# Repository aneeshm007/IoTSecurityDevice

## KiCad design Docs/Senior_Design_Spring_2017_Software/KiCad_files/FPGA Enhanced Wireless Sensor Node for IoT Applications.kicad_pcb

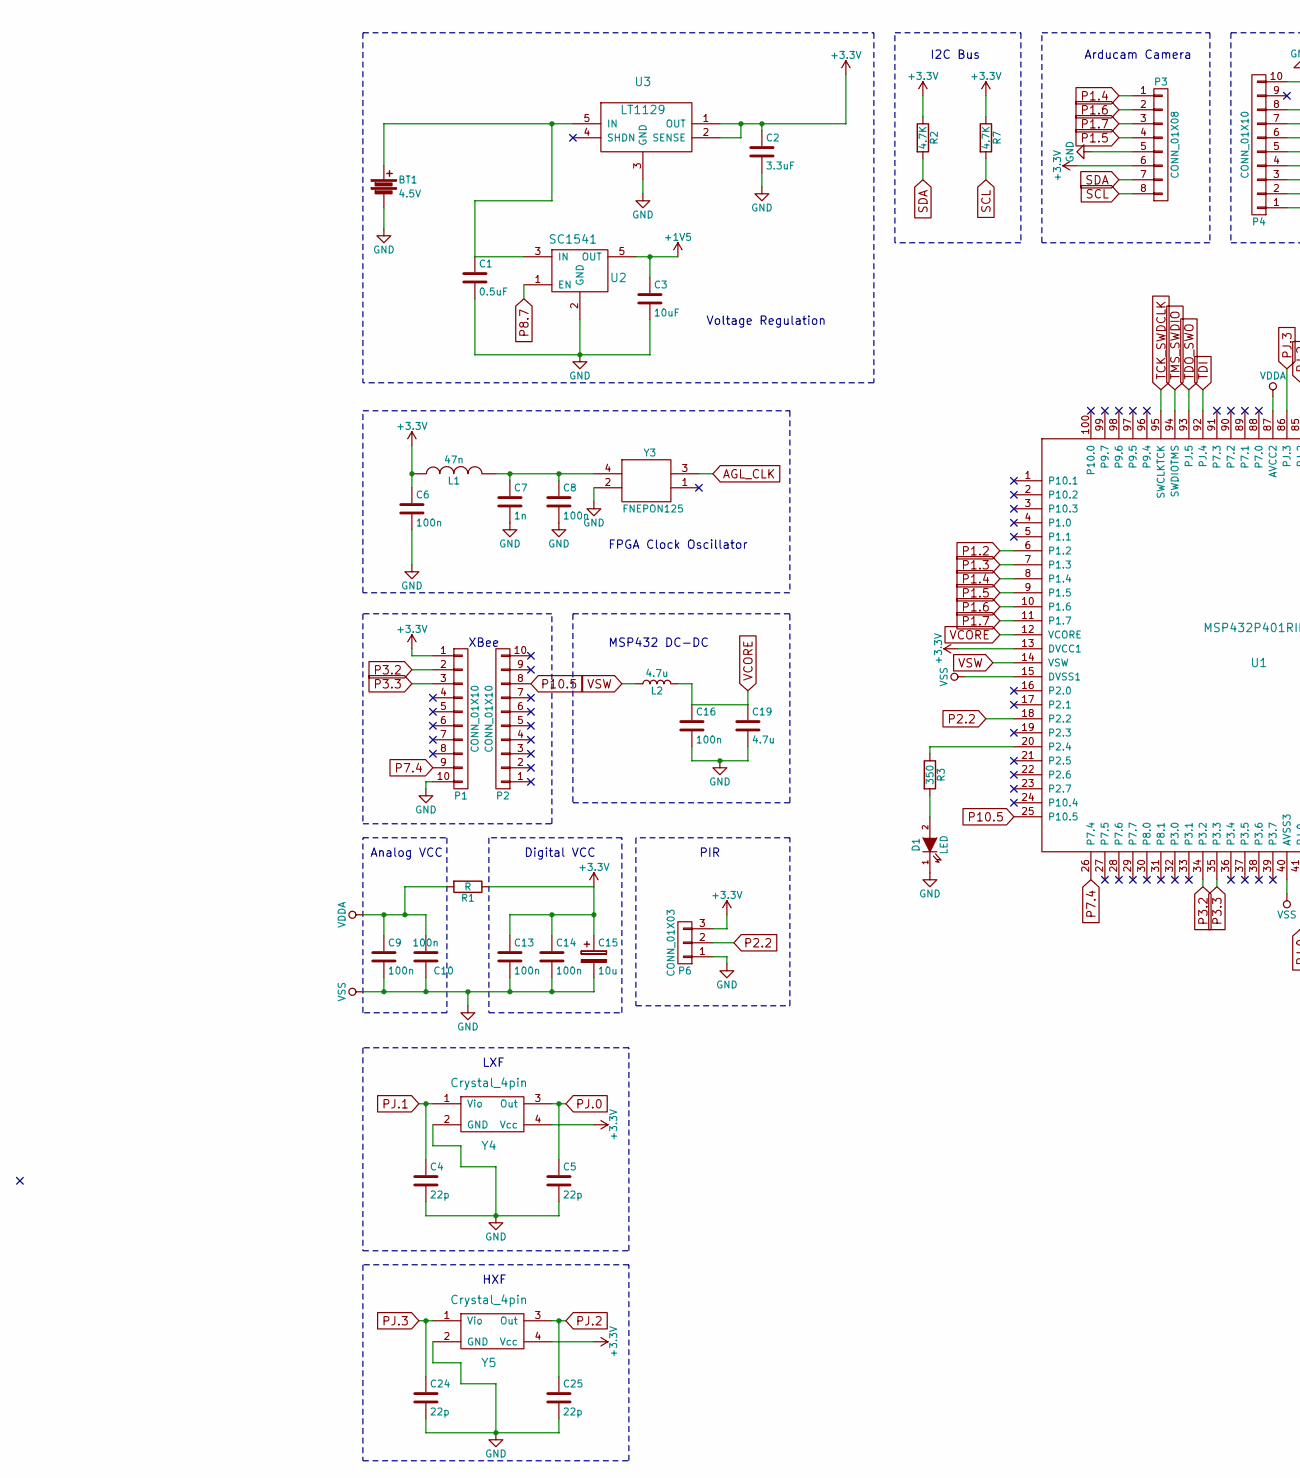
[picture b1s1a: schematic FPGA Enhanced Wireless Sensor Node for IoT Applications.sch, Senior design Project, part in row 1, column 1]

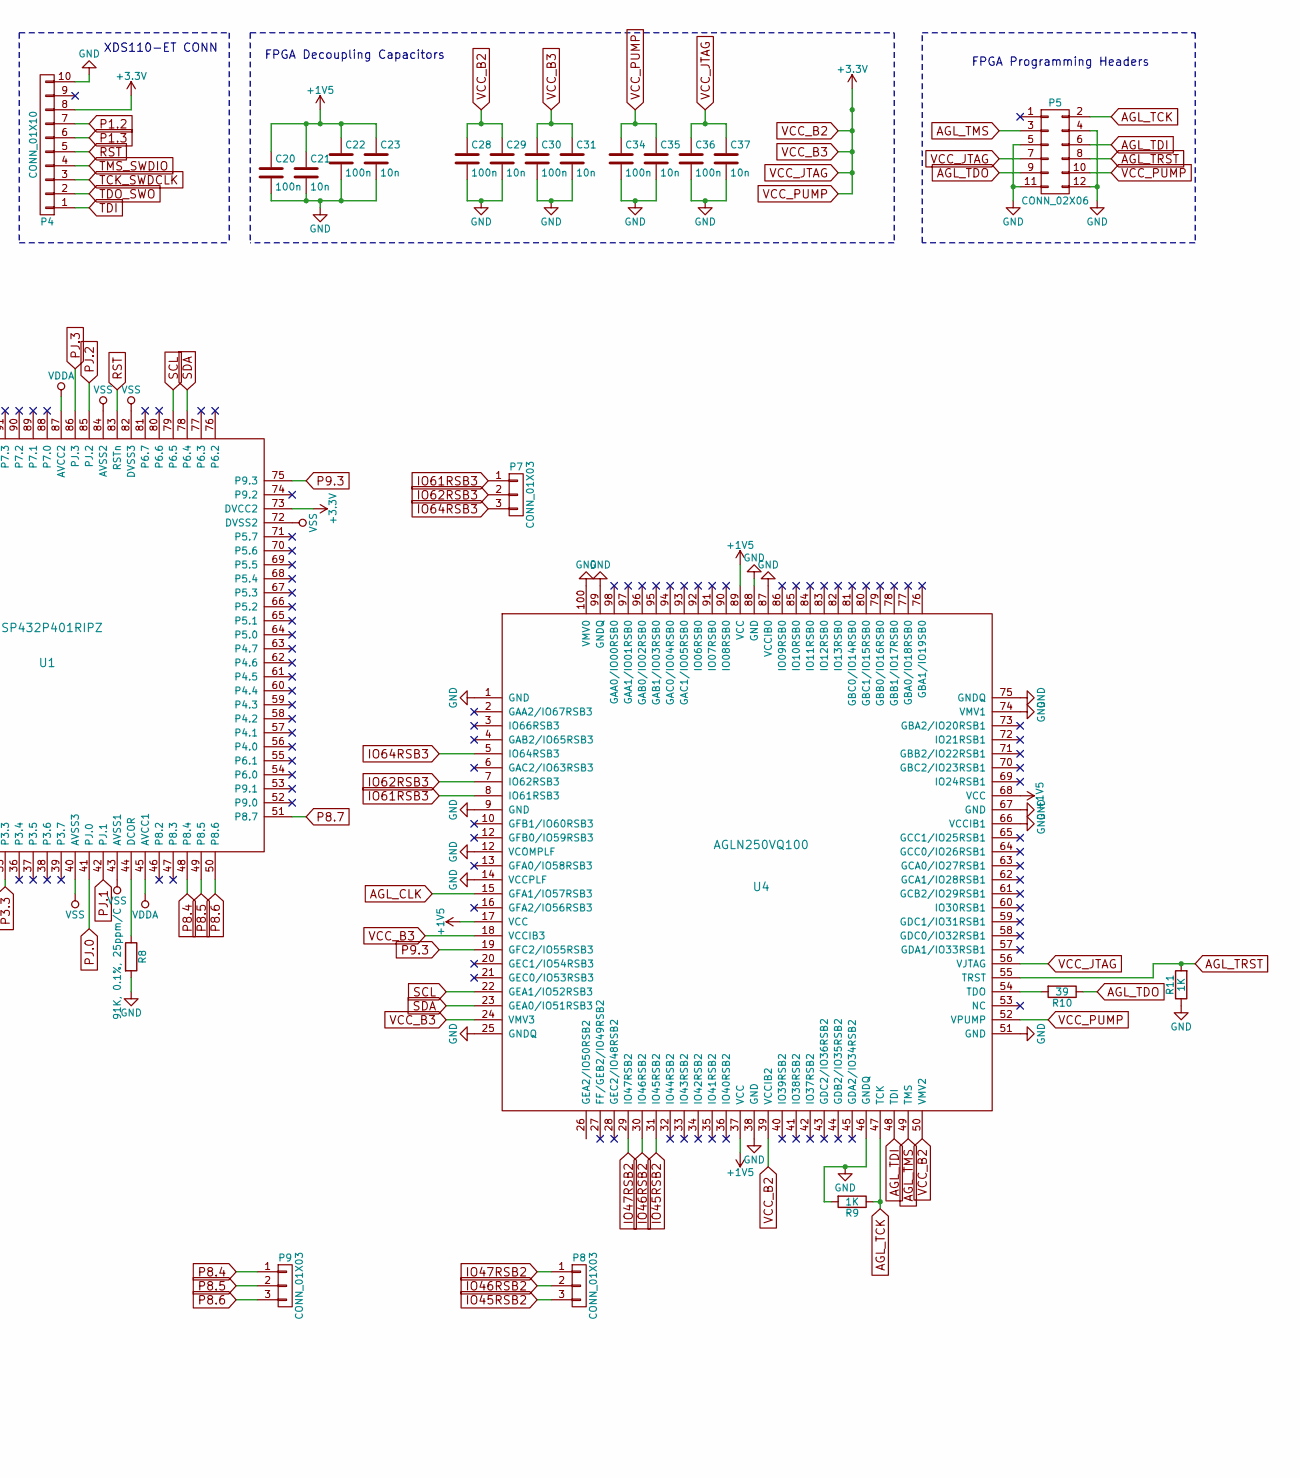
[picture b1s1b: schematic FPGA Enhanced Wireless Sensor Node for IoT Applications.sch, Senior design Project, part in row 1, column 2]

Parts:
BT1: 4.5V; Pin_Header_Straight_1x02_Pitch2.54mm
C1: 0.5uF; C_0603_HandSoldering
C2: 3.3uF; C_0805_HandSoldering
C3: 10uF; C_0805_HandSoldering
C4, C5, C24, C25: 22p; C_0603_HandSoldering
C6, C8, C9, C10, C13, C14, C16, C20, C22, C28, C30, C34, C36: 100n; C_0603_HandSoldering
C7: 1n; C_0603_HandSoldering
C15: 10u; C_0805_HandSoldering
C19: 4.7u; C_0603_HandSoldering
C21, C23, C29, C31, C35, C37: 10n; C_0603_HandSoldering
D1: LED; LED_0805
L1: 47n; C_0603_HandSoldering
L2: 4.7u; C_0603_HandSoldering
P1, P2: CONN_01X10; Pin_Header_Straight_1x10_Pitch2.00mm
P3: CONN_01X08; Pin_Header_Straight_1x08_Pitch2.54mm
P4: CONN_01X10; Pin_Header_Straight_1x10_Pitch2.54mm
P5: CONN_02X06; Pin_Header_Angled_2x06_Pitch2.54mm
P6, P7, P8, P9: CONN_01X03; Pin_Header_Straight_1x03_Pitch2.54mm
R1: R; R_0805_HandSoldering
R2, R7: 4.7K; R_0603_HandSoldering
R3: 350; R_0805_HandSoldering
R8: 91K, 0.1%, 25ppm/C; R_0805_HandSoldering
R9, R11: 1K; R_0805_HandSoldering
R10: 39; R_0603_HandSoldering
U1: MSP432P401RIPZ; LQFP-100_14x14mm_Pitch0.5mm
U2: SC1541; SO-8
U3: LT1129; TO-263-5Lead
U4: AGLN250VQ100; LQFP-100_14x14mm_Pitch0.5mm
Y3: FNEPON125; SOJ-4
Y4: Crystal_4pin; SOJ-4
Y5: Crystal_4pin; SOT-753_(TSOP-5)_Handsoldering

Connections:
+1V5: C3.1, C20.1, C21.1, C22.1, C23.1, U2.5 (OUT), U4.17 (VCC), U4.37 (VCC), U4.68 (VCC), U4.89 (VCC)
AGL_CLK: U4.15 (GFA1/IO57RSB3), Y3.3 (OUT)
AGL_TCK: P5.2, R9.1, U4.47 (TCK)
AGL_TDI: P5.6, U4.48 (TDI)
AGL_TDO: P5.9, R10.1
AGL_TMS: P5.3, U4.49 (TMS)
AGL_TRST: P5.8, R11.2, U4.55 (TRST)
IO45RSB2: P8.3, U4.31 (IO45RSB2)
IO46RSB2: P8.2, U4.30 (IO46RSB2)
IO47RSB2: P8.1, U4.29 (IO47RSB2)
IO61RSB3: P7.1, U4.8 (IO61RSB3)
IO62RSB3: P7.2, U4.7 (IO62RSB3)
IO64RSB3: P7.3, U4.5 (IO64RSB3)
unnamed: BT1.1, C1.1, U2.3 (IN), U3.5 (IN)
unnamed: C7.1, C8.1, L1.2, Y3.4 (VCC)
unnamed: D1.2 (A), R3.2
unnamed: R3.1, U1.20 (P2.4)
unnamed: R8.1, U1.44 (DCOR)
unnamed: R10.2, U4.54 (TDO)
P1.2: P4.7, U1.6 (P1.2)
P1.3: P4.6, U1.7 (P1.3)
P1.4: P3.1, U1.8 (P1.4)
P1.5: P3.4, U1.9 (P1.5)
P1.6: P3.2, U1.10 (P1.6)
P1.7: P3.3, U1.11 (P1.7)
P2.2: P6.2, U1.18 (P2.2)
P3.2: P1.2, U1.34 (P3.2)
P3.3: P1.3, U1.35 (P3.3)
P7.4: P1.9, U1.26 (P7.4)
P8.4: P9.1, U1.48 (P8.4)
P8.5: P9.2, U1.49 (P8.5)
P8.6: P9.3, U1.50 (P8.6)
P8.7: U1.51 (P8.7), U2.1 (EN)
P9.3: U1.75 (P9.3), U4.19 (GFC2/IO55RSB3)
P10.5: P2.8, U1.25 (P10.5)
PJ.0: C5.1, U1.41 (PJ.0), Y4.3 (Out)
PJ.1: C4.1, U1.42 (PJ.1), Y4.1 (Vio)
PJ.2: C25.1, U1.85 (PJ.2), Y5.3 (Out)
PJ.3: C24.1, U1.86 (PJ.3), Y5.1 (Vio)
RST: P4.5, U1.83 (RSTn)
SCL: P3.8, R7.2, U1.79 (P6.5), U4.22 (GEA1/IO52RSB3)
SDA: P3.7, R2.2, U1.78 (P6.4), U4.23 (GEA0/IO51RSB3)
TCK_SWDCLK: P4.3, U1.95 (SWCLKTCK)
TDI: P4.1, U1.92 (PJ.4)
TDO_SWO: P4.2, U1.93 (PJ.5)
TMS_SWDIO: P4.4, U1.94 (SWDIOTMS)
VCC_B2: C2.1, C6.1, C13.1, C14.1, C15.1, C28.1, C29.1, C30.1, C31.1, C34.1, C35.1, C36.1, C37.1, L1.1, P1.1, P3.6, P4.8, P5.7, P5.10, P6.3, R1.1, R2.1, R7.1, U1.13 (DVCC1), U1.73 (DVCC2), U3.1 (OUT), U3.2 (SENSE), U4.18 (VCCIB3), U4.24 (VMV3), U4.39 (VCCIB2), U4.50 (VMV2), U4.52 (VPUMP), U4.56 (VJTAG), Y4.4 (Vcc), Y5.4 (Vcc)
VCORE: C16.1, C19.1, L2.2, U1.12 (VCORE)
VDDA: C9.1, C10.1, R1.2, U1.45 (AVCC1), U1.87 (AVCC2)
VSW: L2.1, U1.14 (VSW)

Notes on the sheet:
XBee
Arducam Camera
FPGA Clock Oscillator
MSP432 DC-DC
Voltage Regulation
I2C Bus
XDS110-ET CONN
Analog VCC
Digital VCC
FPGA Decoupling Capacitors
FPGA Programming Headers
PIR
LXF
HXF

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
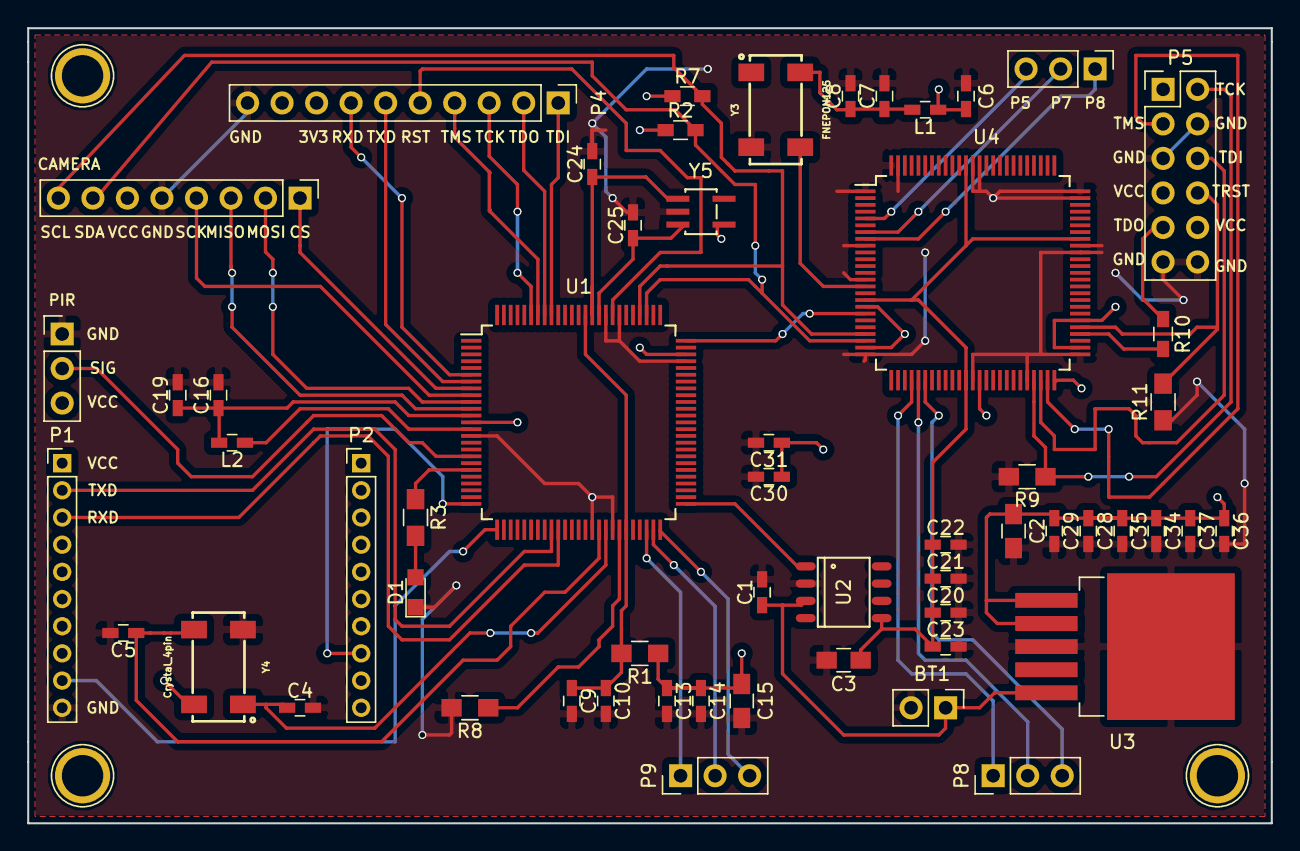
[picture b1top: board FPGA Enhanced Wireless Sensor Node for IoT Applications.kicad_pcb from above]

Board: 2 copper layers, 91.5 x 58.5 mm, 57 parts (0 on the bottom side), 51 nets.

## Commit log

2018-02-02 This is the initial gantt chart we will update this to keep track of our schedule. Feel free to add tasks/goals within your section.
2018-02-11 Added previous documentation
2018-02-21 Completed first draft of the proposal presentation
2018-02-23 Added the outline draft
2018-03-05 Completed the top-down outline for this week
2018-03-25 Progress on Proposal 3/25
2018-04-05 Proposal Slides/Propsoal Presentation
